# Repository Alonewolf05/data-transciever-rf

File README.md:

# data-transciever-rf
Sensor Data Transciever Through RF

There are 4 parts in this board.
- Nucleo-32 Board
- BNO055 IMU
- nRF2401 RF Transciever
- Boost converter

Boost converter is for Li-Ion battery powered applications.
It boosts the voltage to the 10V and power the nucleo through Vin pin.
10V is choosen because Nucleo's ST-Link MCU works from Vin pin. **NOT 5V or 3.3V**

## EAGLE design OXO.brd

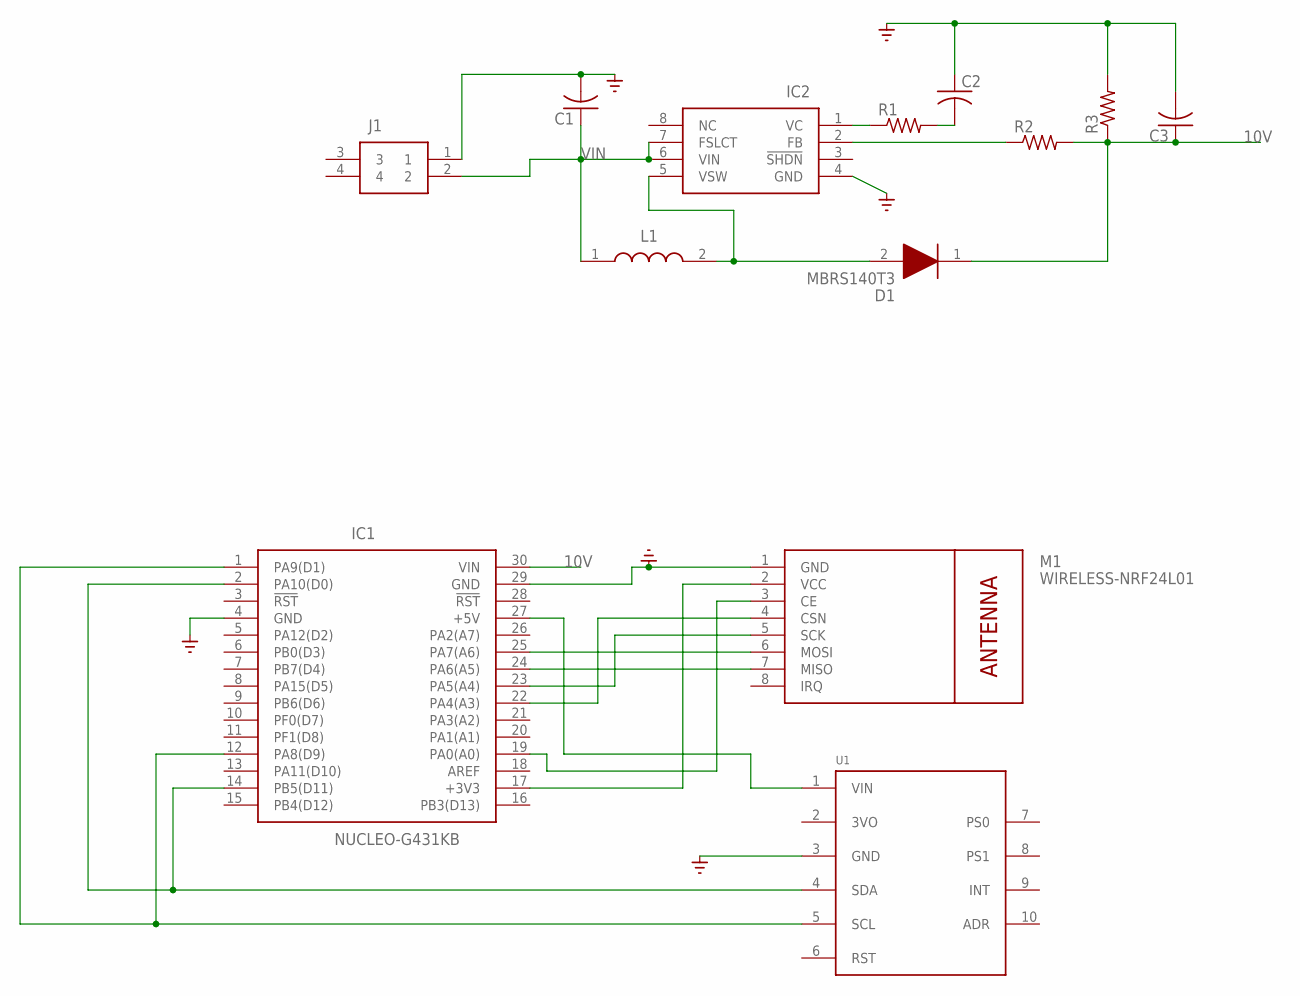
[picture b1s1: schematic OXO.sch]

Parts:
C1, C2, C3: C-USC1206; C1206
D1: MBRS140T3; DIOM5436X247N
IC1: NUCLEO-G431KB; DIPS1524W66P254L5029H1500Q30N
IC2: LM2698MM-ADJ_NOPB; SOP65P490X110-8N
J1: 53398-0271; 533980271
L1: LQH3NPN100MMEL
M1: WIRELESS-NRF24L01
R1, R2, R3: R-US_R1206; R1206
U1: ADADRUIT-BNO055; ADAFRUIT-BNO055

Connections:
3VO: U1.2 (3VO)
10V: C3.1, D1.1 (K), IC1.30 (VIN), R2.2, R3.1
GND: C1.2, C2.1, C3.2, IC1.4 (GND), IC1.29 (GND), IC2.4 (GND), J1.1, M1.1 (GND), R3.2, U1.3 (GND)
unnamed: IC1.17 (+3V3), M1.2 (VCC)
unnamed: IC1.22 (PA4(A3)), M1.4 (CSN)
unnamed: IC1.23 (PA5(A4)), M1.5 (SCK)
unnamed: IC1.24 (PA6(A5)), M1.7 (MISO)
unnamed: IC1.25 (PA7(A6)), M1.6 (MOSI)
unnamed: IC1.27 (+5V), U1.1 (VIN)
unnamed: IC1.1 (PA9(D1)), IC1.12 (PA8(D9)), U1.5 (SCL)
unnamed: IC1.2 (PA10(D0)), IC1.14 (PB5(D11)), U1.4 (SDA)
unnamed: IC1.19 (PA0(A0)), M1.3 (CE)
unnamed: IC2.1 (VC), R1.1
unnamed: C2.2, R1.2
unnamed: IC2.2 (FB), R2.1
unnamed: D1.2 (A), IC2.5 (VSW), L1.2
VIN: C1.1, IC2.6 (VIN), IC2.7 (FSLCT), J1.2, L1.1

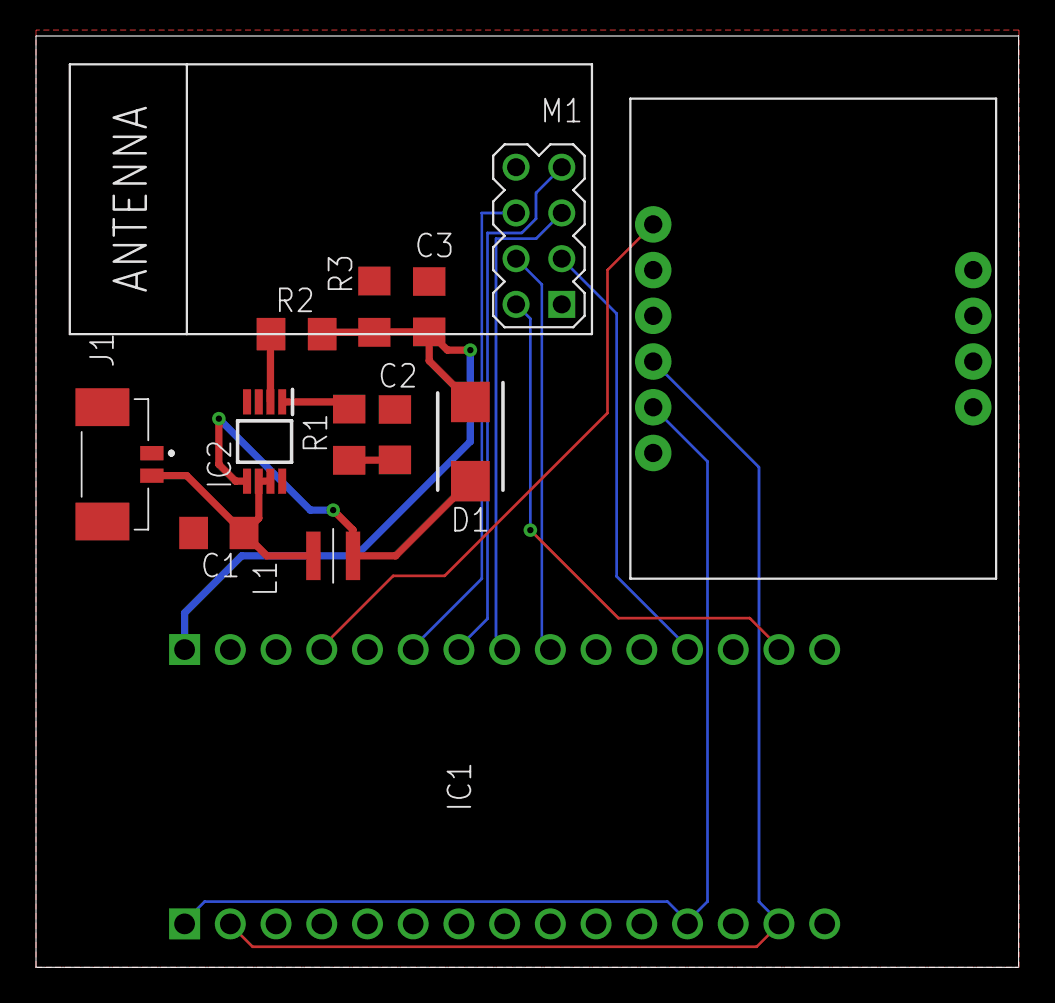
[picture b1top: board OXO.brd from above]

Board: 2 copper layers, 54.6 x 51.7 mm, 13 parts (0 on the bottom side), 16 nets.

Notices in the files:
parts and their libraries:
diy-modules: Released under the Creative Commons Attribution 4.0 International License: http://creativecommons.org/licenses/by/4.0
